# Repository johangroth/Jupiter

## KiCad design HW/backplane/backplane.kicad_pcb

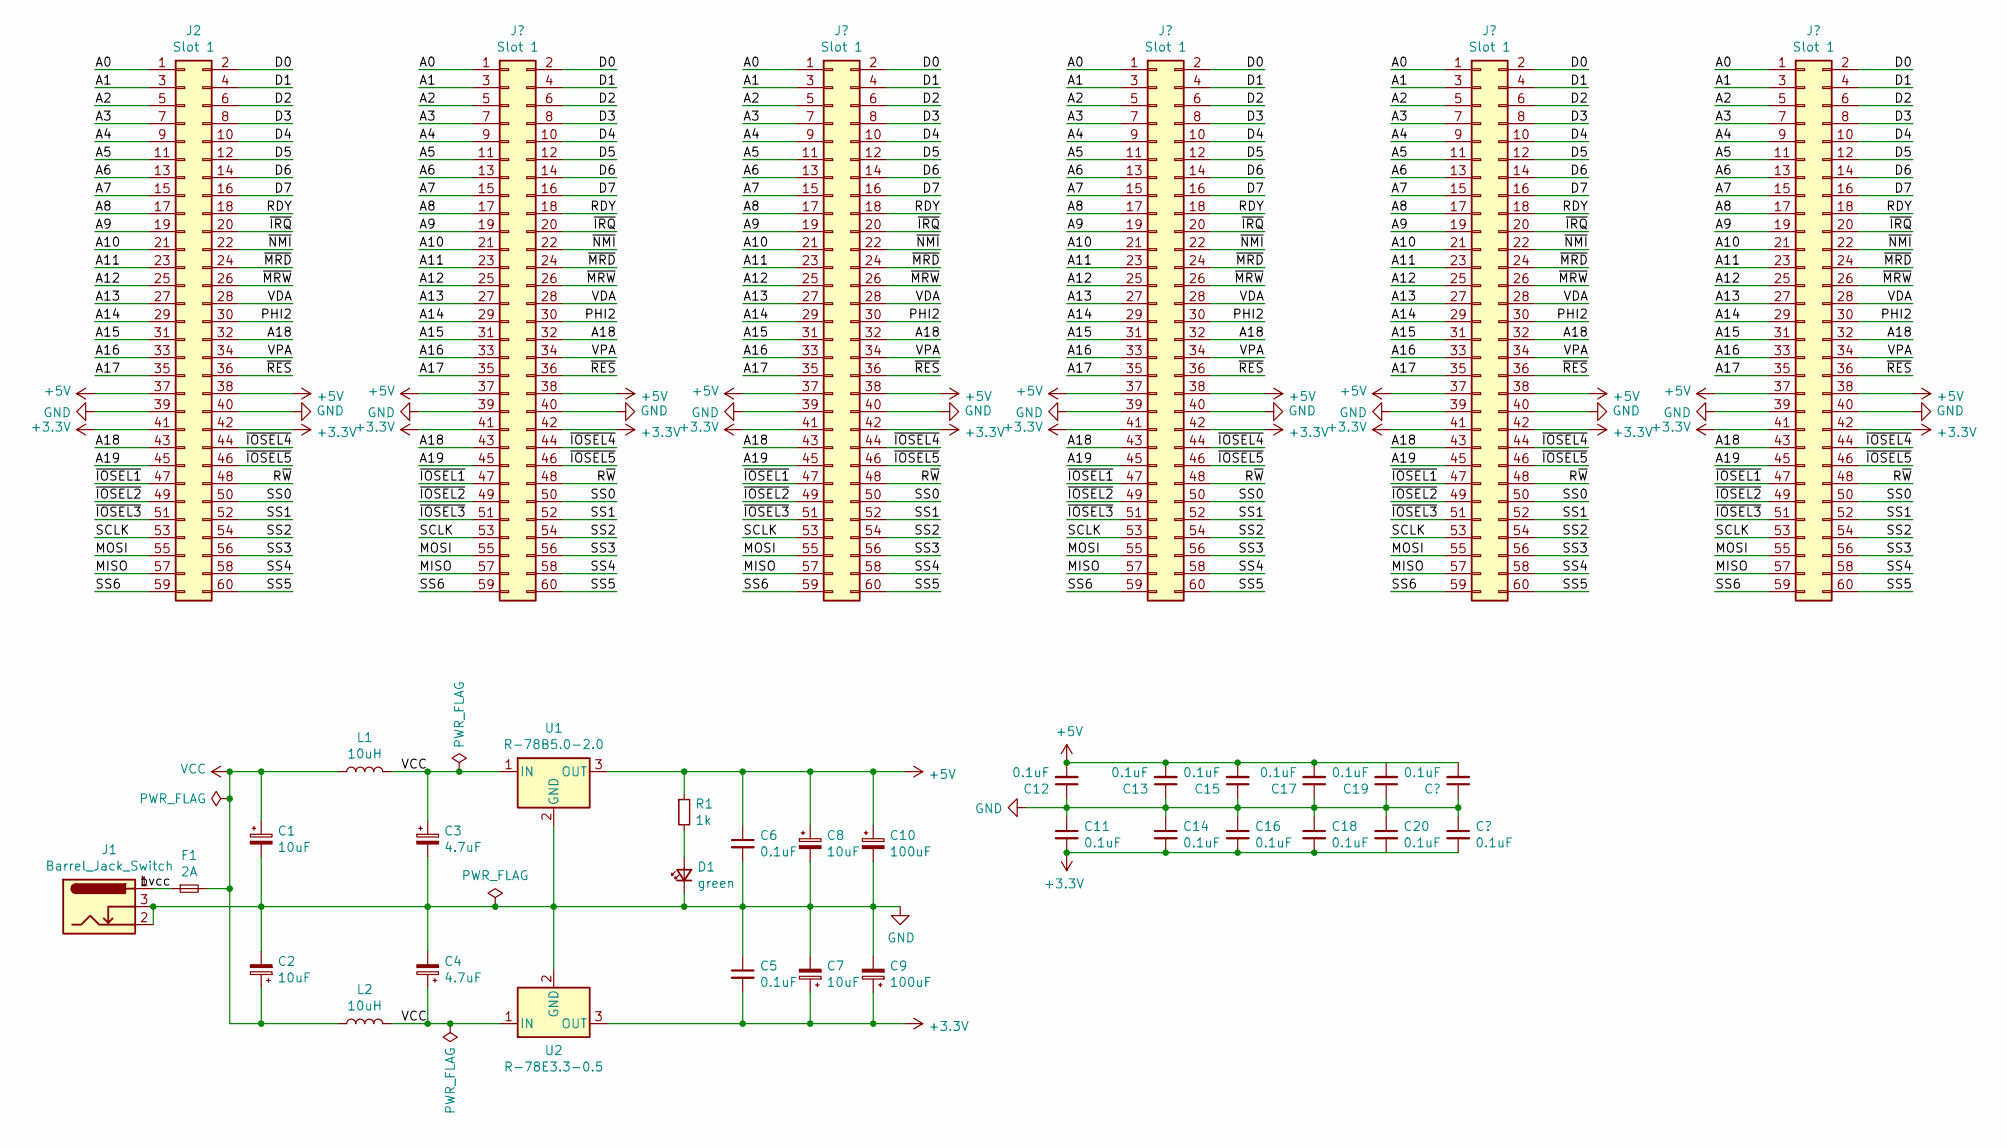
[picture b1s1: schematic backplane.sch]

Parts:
C1, C2, C7, C8: 10uF; CP_Radial_D5.0mm_P2.00mm
C3, C4: 4.7uF; CP_Radial_D5.0mm_P2.00mm
C5, C6, C11, C12, C13, C14, C15, C16, C17, C18, C19, C20: 0.1uF; C_Radial_D4.0mm_H5.0mm_P1.50mm
C9, C10: 100uF; CP_Radial_D5.0mm_P2.00mm
D1: green; LED_D3.0mm
F1: 2A; FUSE_0154004.DR
J1: Barrel_Jack_Switch; BarrelJack_Horizontal
J2: Slot 1; PinSocket_2x30_P2.54mm_Vertical
L1, L2: 10uH; L_Radial_D7.0mm_P3.00mm
R1: 1k; R_Axial_DIN0411_L9.9mm_D3.6mm_P7.62mm_Vertical
U1: R-78B5.0-2.0; Converter_DCDC_RECOM_R-78B-2.0_THT
U2: R-78E3.3-0.5; Converter_DCDC_RECOM_R-78E-0.5_THT

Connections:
+3V3: C5.2, C7.1, C9.1, C11.2, C14.2, C16.2, C18.2, C20.2, J2.41, J2.42, U2.3 (OUT); also elsewhere on the board
+5V: C6.1, C8.1, C10.1, C12.2, C13.2, C15.2, C17.2, C19.2, J2.37, J2.38, R1.1, U1.3 (OUT); also elsewhere on the board
/A0: J2.1; also elsewhere on the board
/A1: J2.3; also elsewhere on the board
/A2: J2.5; also elsewhere on the board
/A3: J2.7; also elsewhere on the board
/A4: J2.9; also elsewhere on the board
/A5: J2.11; also elsewhere on the board
/A6: J2.13; also elsewhere on the board
/A7: J2.15; also elsewhere on the board
/A8: J2.17; also elsewhere on the board
/A9: J2.19; also elsewhere on the board
/A10: J2.21; also elsewhere on the board
/A11: J2.23; also elsewhere on the board
/A12: J2.25; also elsewhere on the board
/A13: J2.27; also elsewhere on the board
/A14: J2.29; also elsewhere on the board
/A15: J2.31; also elsewhere on the board
/A16: J2.33; also elsewhere on the board
/A17: J2.35; also elsewhere on the board
/D0: J2.2; also elsewhere on the board
/D1: J2.4; also elsewhere on the board
/D2: J2.6; also elsewhere on the board
/D3: J2.8; also elsewhere on the board
/D4: J2.10; also elsewhere on the board
/D5: J2.12; also elsewhere on the board
/D6: J2.14; also elsewhere on the board
/D7: J2.16; also elsewhere on the board
/MISO: J2.57; also elsewhere on the board
/MOSI: J2.55; also elsewhere on the board
/PHI2: J2.30; also elsewhere on the board
/RDY: J2.18; also elsewhere on the board
/R~W: J2.48; also elsewhere on the board
/SCLK: J2.53; also elsewhere on the board
/SS0: J2.50; also elsewhere on the board
/SS1: J2.52; also elsewhere on the board
/SS2: J2.54; also elsewhere on the board
/SS3: J2.56; also elsewhere on the board
/SS4: J2.58; also elsewhere on the board
/SS5: J2.60; also elsewhere on the board
/SS6: J2.59; also elsewhere on the board
/VDA: J2.28; also elsewhere on the board
/VPA: J2.34; also elsewhere on the board
/bvcc: F1.1, J1.1
/~IOSEL1: J2.47; also elsewhere on the board
/~IOSEL2: J2.49; also elsewhere on the board
/~IOSEL3: J2.51; also elsewhere on the board
/~IOSEL4: J2.44; also elsewhere on the board
/~IOSEL5: J2.46; also elsewhere on the board
/~IRQ: J2.20; also elsewhere on the board
/~MRW: J2.45; also elsewhere on the board
/~NMI: J2.24; also elsewhere on the board
/~RES: J2.36; also elsewhere on the board
GND: C1.2, C2.2, C3.2, C4.2, C5.1, C6.2, C7.2, C8.2, C9.2, C10.2, C11.1, C12.1, C13.1, C14.1, C15.1, C16.1, C17.1, C18.1, C19.1, C20.1, D1.1 (K), J1.2, J1.3, J2.39, J2.40, U1.2 (GND), U2.2 (GND); also elsewhere on the board
unnamed: D1.2 (A), R1.2
VCC: C1.1, C2.1, C3.1, C4.1, F1.2, L1.1, L1.2, L2.1, L2.2, U1.1 (IN), U2.1 (IN)

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
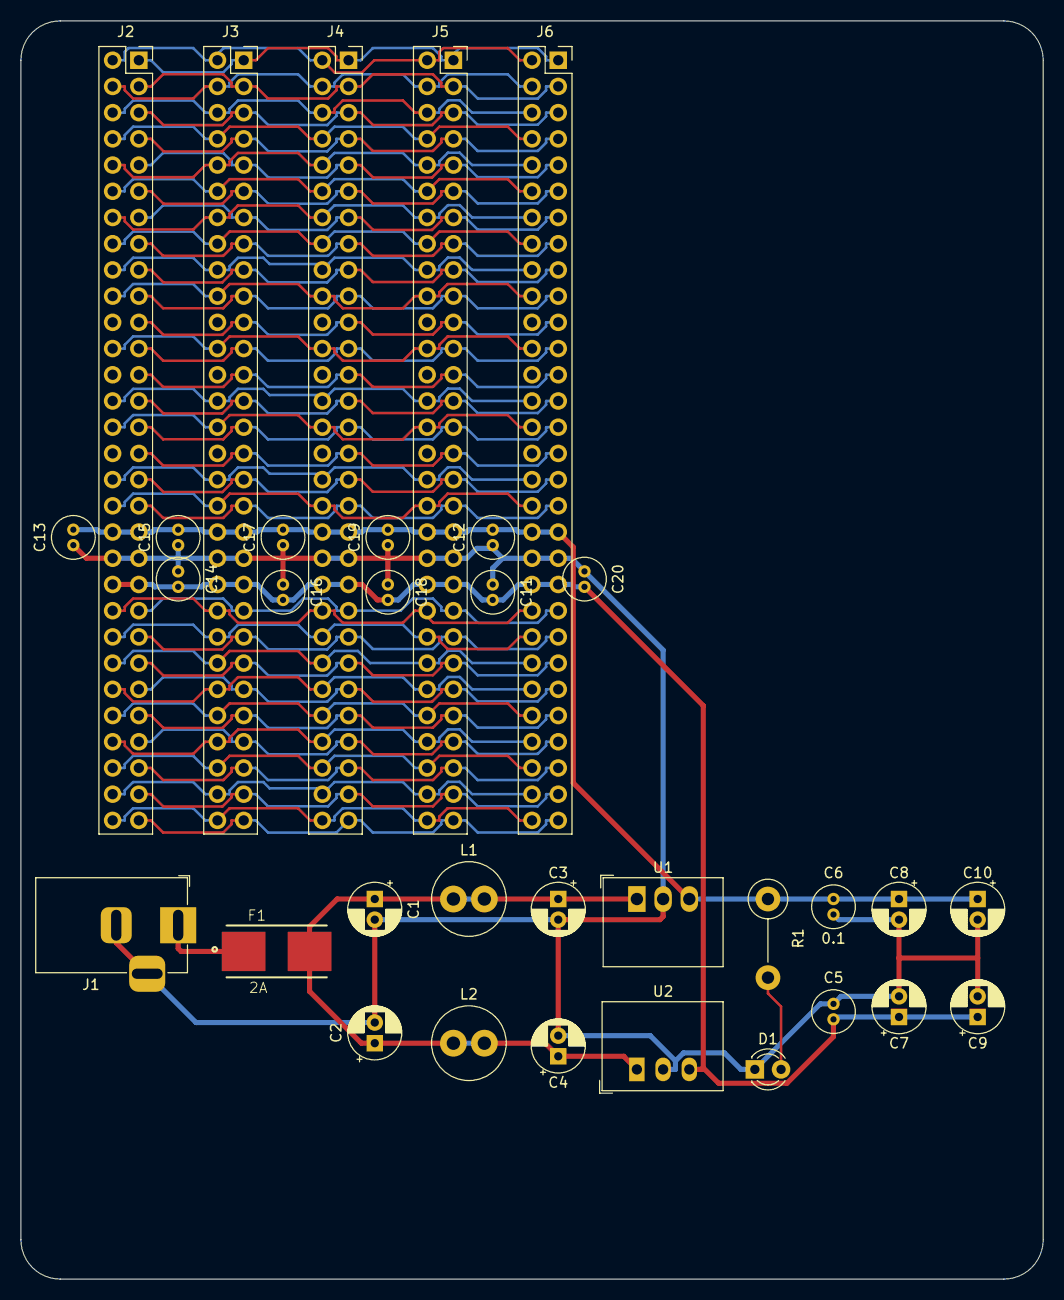
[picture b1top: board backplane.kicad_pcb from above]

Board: 2 copper layers, 99.1 x 121.9 mm, 33 parts (0 on the bottom side), 57 nets.

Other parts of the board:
J3: Slot 2; PinSocket_2x30_P2.54mm_Vertical
J4: Slot 3; PinSocket_2x30_P2.54mm_Vertical
J5: Slot 4; PinSocket_2x30_P2.54mm_Vertical
J6: Slot 5; PinSocket_2x30_P2.54mm_Vertical

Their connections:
+3V3: J3.41, J3.42, J4.41, J4.42, J5.41, J5.42, J6.41, J6.42; also elsewhere on the board
+5V: J3.37, J3.38, J4.37, J4.38, J5.37, J5.38, J6.37, J6.38; also elsewhere on the board
/A0: J3.1, J4.1, J5.1, J6.1; also elsewhere on the board
/A1: J3.3, J4.3, J5.3, J6.3; also elsewhere on the board
/A2: J3.5, J4.5, J5.5, J6.5; also elsewhere on the board
/A3: J3.7, J4.7, J5.7, J6.7; also elsewhere on the board
/A4: J3.9, J4.9, J5.9, J6.9; also elsewhere on the board
/A5: J3.11, J4.11, J5.11, J6.11; also elsewhere on the board
/A6: J3.13, J4.13, J5.13, J6.13; also elsewhere on the board
/A7: J3.15, J4.15, J5.15, J6.15; also elsewhere on the board
/A8: J3.17, J4.17, J5.17, J6.17; also elsewhere on the board
/A9: J3.19, J4.19, J5.19, J6.19; also elsewhere on the board
/A10: J3.21, J4.21, J5.21, J6.21; also elsewhere on the board
/A11: J3.23, J4.23, J5.23, J6.23; also elsewhere on the board
/A12: J3.25, J4.25, J5.25, J6.25; also elsewhere on the board
/A13: J3.27, J4.27, J5.27, J6.27; also elsewhere on the board
/A14: J3.29, J4.29, J5.29, J6.29; also elsewhere on the board
/A15: J3.31, J4.31, J5.31, J6.31; also elsewhere on the board
/A16: J3.33, J4.33, J5.33, J6.33; also elsewhere on the board
/A17: J3.35, J4.35, J5.35, J6.35; also elsewhere on the board
/D0: J3.2, J4.2, J5.2, J6.2; also elsewhere on the board
/D1: J3.4, J4.4, J5.4, J6.4; also elsewhere on the board
/D2: J3.6, J4.6, J5.6, J6.6; also elsewhere on the board
/D3: J3.8, J4.8, J5.8, J6.8; also elsewhere on the board
/D4: J3.10, J4.10, J5.10, J6.10; also elsewhere on the board
/D5: J3.12, J4.12, J5.12, J6.12; also elsewhere on the board
/D6: J3.14, J4.14, J5.14, J6.14; also elsewhere on the board
/D7: J3.16, J4.16, J5.16, J6.16; also elsewhere on the board
/MISO: J3.57, J4.57, J5.57, J6.57; also elsewhere on the board
/MOSI: J3.55, J4.55, J5.55, J6.55; also elsewhere on the board
/PHI2: J3.30, J4.30, J5.30, J6.30; also elsewhere on the board
/RDY: J3.18, J4.18, J5.18, J6.18; also elsewhere on the board
/R~W: J3.48, J4.48, J5.48, J6.48; also elsewhere on the board
/SCLK: J3.53, J4.53, J5.53, J6.53; also elsewhere on the board
/SS0: J3.50, J4.50, J5.50, J6.50; also elsewhere on the board
/SS1: J3.52, J4.52, J5.52, J6.52; also elsewhere on the board
/SS2: J3.54, J4.54, J5.54, J6.54; also elsewhere on the board
/SS3: J3.56, J4.56, J5.56, J6.56; also elsewhere on the board
/SS4: J3.58, J4.58, J5.58, J6.58; also elsewhere on the board
/SS5: J3.60, J4.60, J5.60, J6.60; also elsewhere on the board
/SS6: J3.59, J4.59, J5.59, J6.59; also elsewhere on the board
/VDA: J3.28, J4.28, J5.28, J6.28; also elsewhere on the board
/VPA: J3.34, J4.34, J5.34, J6.34; also elsewhere on the board
/~IOSEL1: J3.47, J4.47, J5.47, J6.47; also elsewhere on the board
/~IOSEL2: J3.49, J4.49, J5.49, J6.49; also elsewhere on the board
/~IOSEL3: J3.51, J4.51, J5.51, J6.51; also elsewhere on the board
/~IOSEL4: J3.44, J4.44, J5.44, J6.44; also elsewhere on the board
/~IOSEL5: J3.46, J4.46, J5.46, J6.46; also elsewhere on the board
/~IRQ: J3.20, J4.20, J5.20, J6.20; also elsewhere on the board
/~MRW: J3.45, J4.45, J5.45, J6.45; also elsewhere on the board
/~NMI: J3.24, J4.24, J5.24, J6.24; also elsewhere on the board
/~RES: J3.36, J4.36, J5.36, J6.36; also elsewhere on the board
GND: J3.39, J3.40, J4.39, J4.40, J5.39, J5.40, J6.39, J6.40; also elsewhere on the board

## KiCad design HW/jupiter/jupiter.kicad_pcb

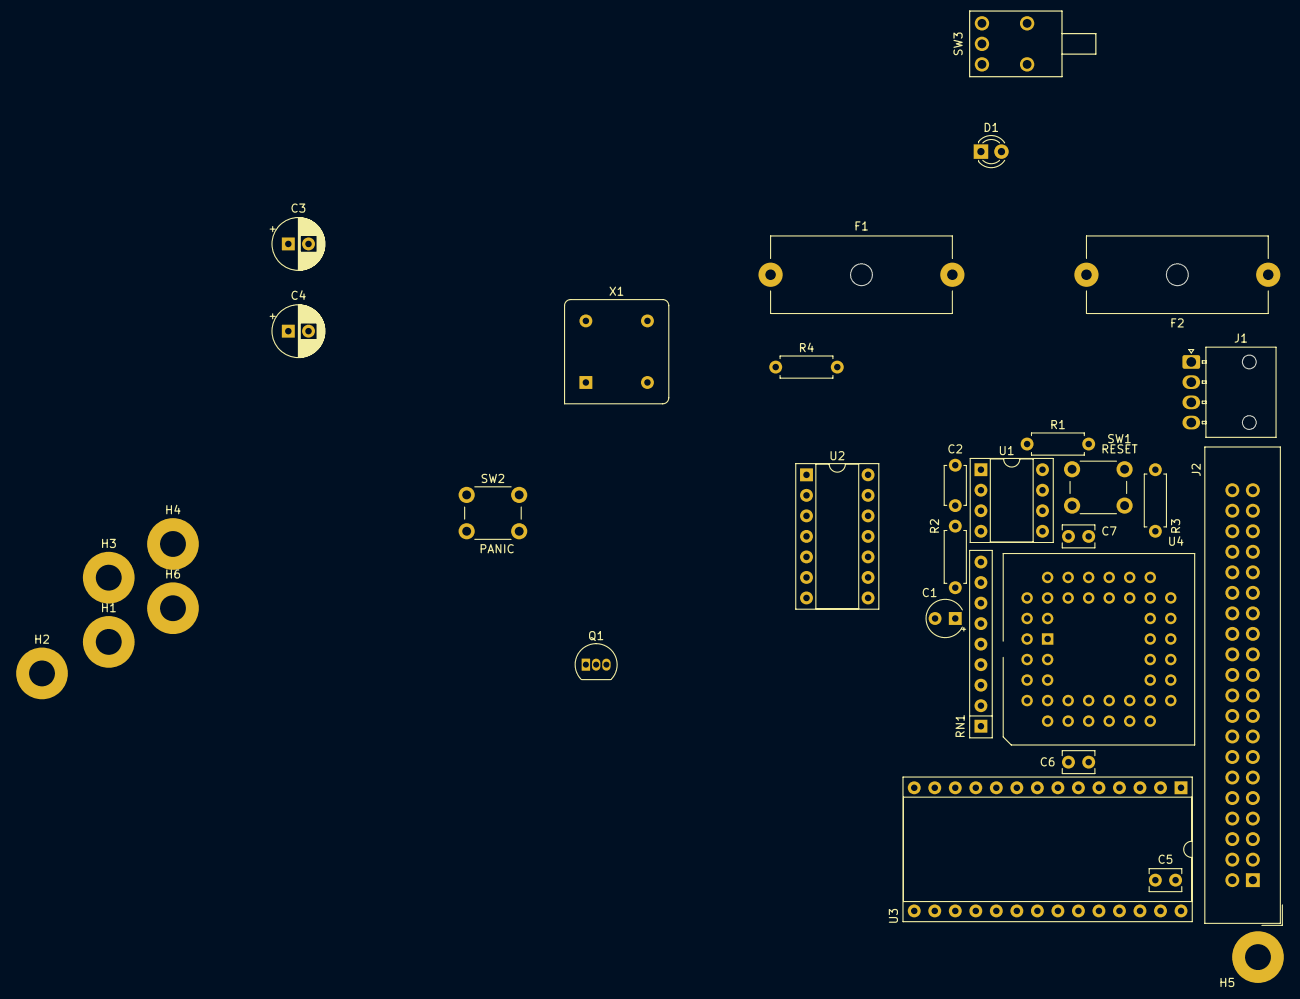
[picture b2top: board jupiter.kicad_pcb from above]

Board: 4 copper layers, 32 parts (0 on the bottom side), 45 nets, no tracks yet.

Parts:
C1: 15uF; CP_Radial_Tantal_D4.5mm_P2.50mm
C2: 0.1uF; C_Disc_D4.7mm_W2.5mm_P5.00mm
C3, C4: 100uF; CP_Radial_D6.3mm_P2.50mm
C5, C6, C7: 0.1uF; C_Disc_D3.8mm_W2.6mm_P2.50mm
D1: LED; LED_D3.0mm
F1: 200mA; Fuseholder_Cylinder-5x20mm_Schurter_0031_8201_Horizontal_Op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
F2: 1A; Fuseholder_Cylinder-5x20mm_Schurter_0031_8201_Horizontal_Op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
H1, H2, H3, H4, H5, H6: MountingHole; MountingHole_3.2mm_M3_Pad
J1: POWER_IN; Molex_Nano-Fit_105313-xx04_1x04_P2.50mm_Horizontal
J2: Expansion Bus; IDC-Header_2x20_P2.54mm_Vertical
Q1: DS1813; TO-92_Inline
R1: 22k; R_Axial_DIN0207_L6.3mm_D2.5mm_P7.62mm_Horizontal
R2, R4: 470; R_Axial_DIN0207_L6.3mm_D2.5mm_P7.62mm_Horizontal
R3: 3.3k; R_Axial_DIN0207_L6.3mm_D2.5mm_P7.62mm_Horizontal
RN1: 3.3k; R_Array_SIP9
SW1: RESET; SW_PUSH_6mm_H4.3mm
SW2: PANIC; SW_PUSH_6mm_H4.3mm
SW3: SPDT; SW-SPDT-0900766b81587629
U1: TL7705B; DIP-8_W7.62mm_Socket
U2: 74HC74; DIP-14_W7.62mm_Socket
U3: DS1511Y+; DIP-28_W15.24mm_Socket
U4: WD65C816S_PLCC44-65xx; PLCC-44_THT-Socket
X1: 16MHz; Oscillator_DIP-8

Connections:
+5V: C3.1, F1.2
/CPU, ROM and RAM/A0: J2.4, U3.10, U4.10
/CPU, ROM and RAM/A1: J2.6, U3.9, U4.11
/CPU, ROM and RAM/A2: J2.8, U3.8, U4.13
/CPU, ROM and RAM/A3: J2.10, U3.7, U4.14
/CPU, ROM and RAM/A4: J2.12, U3.6, U4.15
/CPU, ROM and RAM/A5: J2.14, U4.16
/CPU, ROM and RAM/A6: J2.16, U4.17
/CPU, ROM and RAM/A7: J2.18, U4.18
/CPU, ROM and RAM/A8: J2.20, U4.19
/CPU, ROM and RAM/A9: J2.22, U4.20
/CPU, ROM and RAM/A10: J2.24, U4.21
/CPU, ROM and RAM/A11: J2.26, U4.22
/CPU, ROM and RAM/A12: J2.28, U4.25
/CPU, ROM and RAM/A13: J2.30, U4.26
/CPU, ROM and RAM/A14: J2.32, U4.27
/CPU, ROM and RAM/A15: J2.34, U4.28
/CPU, ROM and RAM/BE: RN1.6, U4.40
/CPU, ROM and RAM/CLK: U2.5, U4.41
/CPU, ROM and RAM/D0: J2.3, U3.11, U4.36
/CPU, ROM and RAM/D1: J2.5, U3.12, U4.35
/CPU, ROM and RAM/D2: J2.7, U3.13, U4.34
/CPU, ROM and RAM/D3: J2.9, U3.15, U4.33
/CPU, ROM and RAM/D4: J2.11, U3.16, U4.32
/CPU, ROM and RAM/D5: J2.13, U3.17, U4.31
/CPU, ROM and RAM/D6: J2.15, U3.18, U4.30
/CPU, ROM and RAM/D7: J2.17, U3.19, U4.29
/CPU, ROM and RAM/RDY: RN1.5, U4.3
/CPU, ROM and RAM/~ABT: RN1.4, U4.4
/CPU, ROM and RAM/~IRQ: RN1.8, U3.5, U4.5
/CPU, ROM and RAM/~NMI: Q1.1, RN1.7, SW2.2, U4.7
/Power and glue/POWER_IN: F2.1, J1.1
/Power and glue/RES: R3.1, RN1.2, U1.5, U1.6, U3.4, U4.44
/Power and glue/~KS: RN1.9, U3.24
/Power and glue/~PWR: RN1.3, U3.1
GND: C1.2, C2.2, C3.2, C4.2, C5.1, C6.2, C7.1, D1.1, J1.2, J1.3, J2.39, J2.40, Q1.3, R3.2, SW1.1, SW2.1, U1.4, U2.7, U2.10, U2.11, U2.12, U2.13, U3.14, U3.21, U3.26, U4.1, U4.23, U4.24, X1.4
unnamed: C1.1, R2.2
unnamed: C2.1, U1.1
unnamed: C4.1, F2.2, SW3.1
unnamed: D1.2, R4.2
unnamed: R1.2, SW1.2, U1.2
unnamed: R2.1, U1.3
unnamed: U2.2, U2.6
unnamed: U2.3, X1.5
VCC: C5.2, C6.1, C7.2, F1.1, J2.1, J2.2, Q1.2, R1.1, R4.1, RN1.1, SW3.2, U1.7, U1.8, U2.1, U2.4, U2.14, U3.28, U4.9, U4.37, X1.8

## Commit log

2019-06-23 Schematics to clock, reset, panic and power section done.
2019-06-23 Added RTC and expansion bus. WIP
2019-06-27 Started PCB. CPU, RTC and support section added.
2019-06-30 Added documentation to ca65 assembler in pdf format.
2019-07-09 Added PCB train technical capabilities.
2019-07-10 started to layout the pcb.
2019-11-19 A lot of new data sheets. Some updates to schema and PCB layout.
2019-11-19 Removed executable flag on document.
2020-09-17 Restructure of HW to make it into modules ala RC2014.
2021-03-28 Restructure of directory tree.
